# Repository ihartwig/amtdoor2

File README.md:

amtdoor2
========

This repository tracks files for AMT Door 2, an RFID based lock system in use at the [Ace Monster Toys](http://acemonstertoys.org/) hackspace in Oakland, CA. A complete description of the system these files are part of, [see the description on the AMT Wiki](http://wiki.acemonstertoys.org/Door#AMT_Door_2).

Included files:
* authCode - code to run on a raspberry pi or similar auth server
* housing - 2D drawings for assembly of the door tag reader
* hwTestCode - simplified panel mcu code to test clock settings
* panelMcuCode - firmware to run on the panel mcu that interprets RFID signals and accepts opening requests from the auth server
* physical - Eagle schematic/boards for the panel mcu

## Setting up on a 16u4:

to flash a new atmega16u4 for this code using an ISP (without the bootloader):

```
$ avrdude -p atmega16u4 -P usb -c avrispmkii -u -U lfuse:w:0xfc:m -U hfuse:w:0xd0:m -U efuse:w:0xc3:m
$ make MCU=atmega16u4
$ avrdude -p atmega16u4 -P usb -c avrispmkii -U flash:w:main.hex
```

to load the bootloader first using an ISP:

```
need to set fuses. we will copy from adafruit atmega32u4 dev board.
adafruit sets to: (E:C3, H:D0, L:FC) (avrdude-- has a typo)

Extended (0 is set):
7 1 Reserved
  1 Reserved
  0 Reserved
  0 Reserved
  0 HWBE          Hardware Boot Enable
  0 BODLEVEL2(1)  Brown-out Detector trigger level
  1 BODLEVEL1(1)  Brown-out Detector trigger level
0 1 BODLEVEL0(1)  Brown-out Detector trigger level

High (0 is set):
7 1 OCDEN         Enable OCD
  1 JTAGEN        Enable JTAG
  0 SPIEN         Enable Serial Program and Data Downloading
  1 WDTON         Watchdog Timer always on
  0 EESAVE        EEPROM memory is preserved through the Chip Erase
  0 BOOTSZ1       Select Boot Size (see Table 28-7 for details)
  0 BOOTSZ0       Select Boot Size (see Table 28-7 for details)
0 0 BOOTRST       Select Bootloader Address as Reset Vector

Low (0 is set):
7 1 CKDIV8        Divide clock by 8
  1 CKOUT         Clock output
  1 SUT1          Select start-up time
  1 SUT0          Select start-up time
  1 CKSEL3        Select Clock source
  1 CKSEL2        Select Clock source
  0 CKSEL1        Select Clock source
0 0 CKSEL0        Select Clock source
```

to compile CDC bootloader (from lufa-lib trunk):
for BOOTSZ1 = BOOTSZ0 = 0. see datasheet table 27-8.

```
$ make MCU=atmega16u4 BOOT_START=0x1800 F_CPU=16000000
$ mv BootloaderCDC.hex BootloaderCDC_16u4.hex
$ avrdude -p atmega16u4 -P usb -c avrispmkii -U flash:w:BootloaderCDC_16u4.hex
```

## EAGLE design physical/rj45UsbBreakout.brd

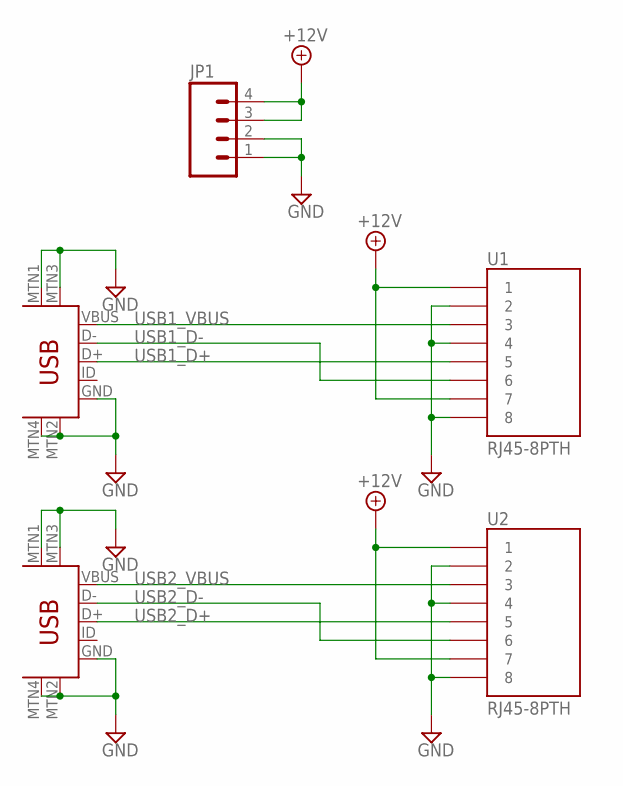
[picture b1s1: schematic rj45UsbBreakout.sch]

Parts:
JP1: M04LOCK; 1X04_LOCK
U1, U2: RJ45-8PTH; RJ45-8
U3, U4: USB-MINIB-5PIN; USB-MINIB

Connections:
+12V: JP1.3, JP1.4, U1.1, U1.7, U2.1, U2.7
GND: JP1.1, JP1.2, U1.2, U1.4, U1.8, U2.2, U2.4, U2.8, U3.GND, U3.MTN1 (MTN2), U3.MTN2 (MTN3), U3.MTN3 (MTN1), U3.MTN4, U4.GND, U4.MTN1 (MTN2), U4.MTN2 (MTN3), U4.MTN3 (MTN1), U4.MTN4
USB1_D+: U1.5, U3.D+
USB1_D-: U1.6, U3.D-
USB1_VBUS: U1.3, U3.VBUS
USB2_D+: U2.5, U4.D+
USB2_D-: U2.6, U4.D-
USB2_VBUS: U2.3, U4.VBUS

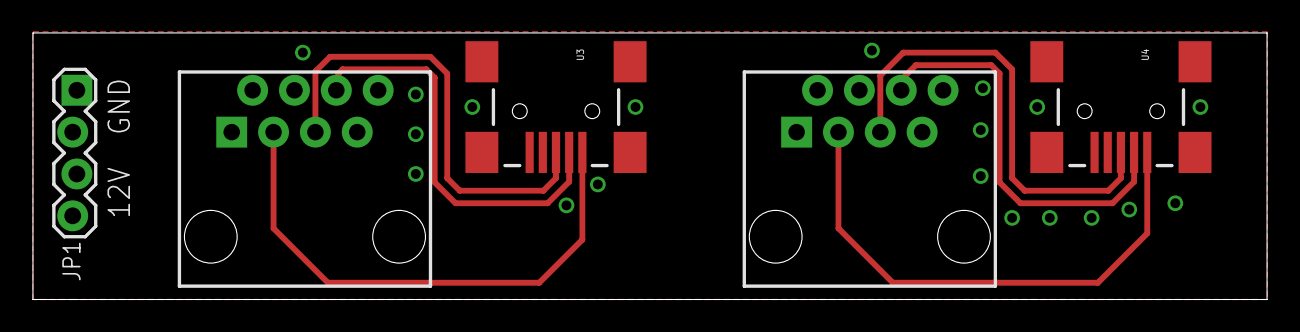
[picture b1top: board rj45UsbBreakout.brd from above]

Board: 2 copper layers, 74.9 x 16.2 mm, 5 parts (0 on the bottom side), 8 nets.

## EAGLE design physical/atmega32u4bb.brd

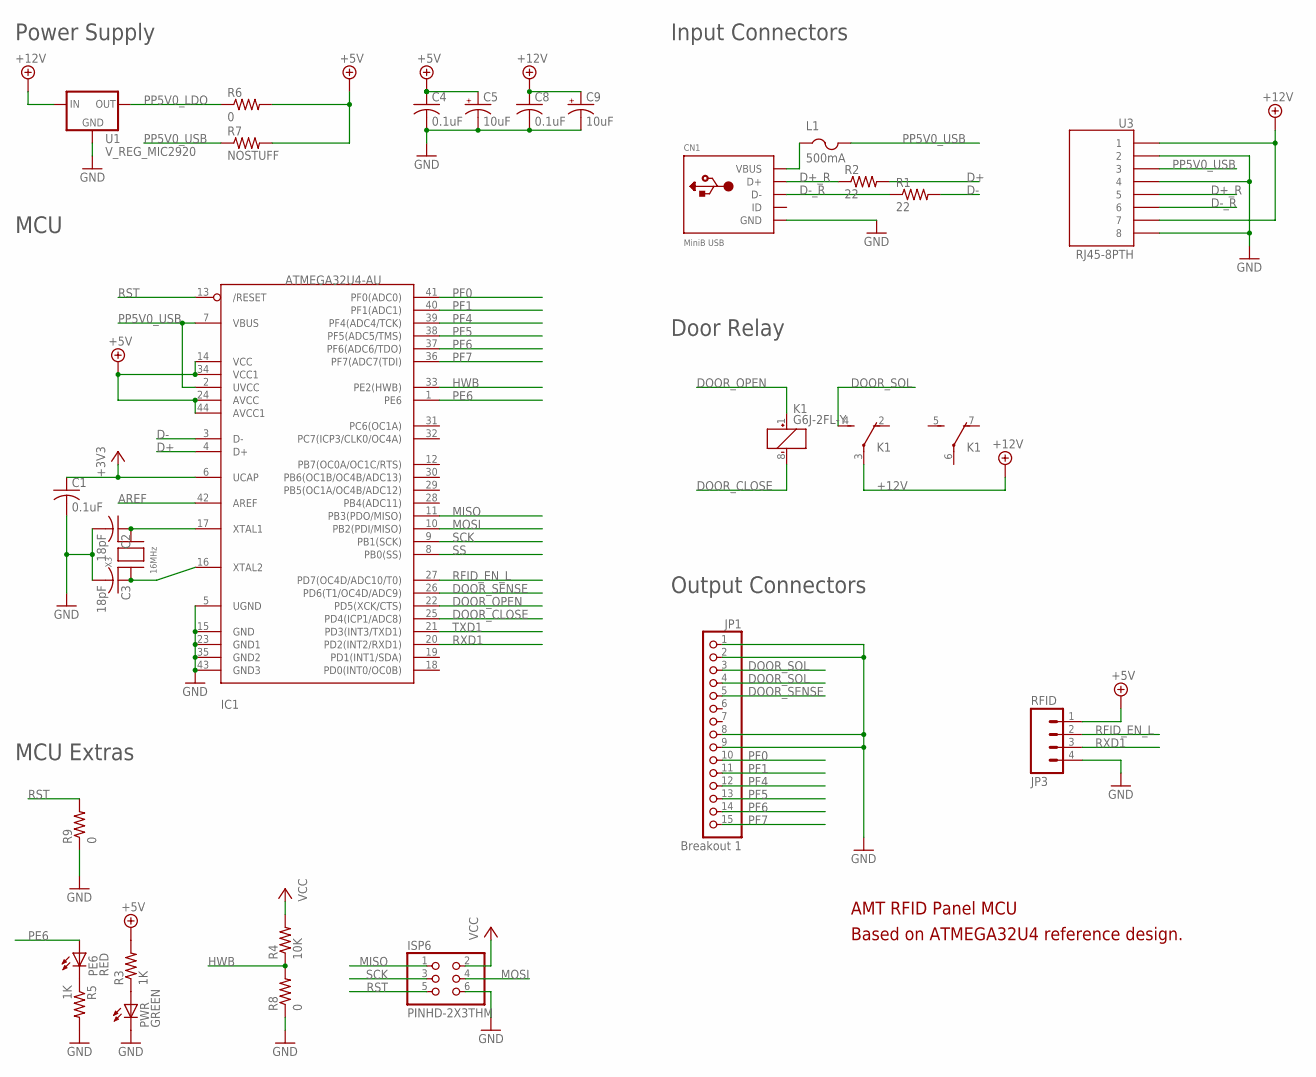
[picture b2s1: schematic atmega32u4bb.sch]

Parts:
C1, C4, C8: 0.1uF; C0805K
C2, C3: 18pF; C0805K
C5, C9: 10uF; A/3216-18R
CN1: MiniB USB; USB-MINIB
IC1: ATMEGA32U4-AU; TQFP44
ISP6: PINHD-2X3THM; ISP6
JP1: Breakout 1; 1X15-CB
JP3: RFID; 1X04_LOCK
K1: G6J-2FL-Y
L1: 500mA; R1206
PE6: RED; CHIPLED_0805
PWR: GREEN; CHIPLED_0805
R1, R2: 22; R0805
R3, R5: 1K; R0805
R4: 10K; R0805
R6, R8, R9: 0; R0805
R7: NOSTUFF; R0805
U1: V_REG_MIC2920; SOT223
U3: RJ45-8PTH; RJ45-8
X3: 16MHz; NX5032

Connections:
+3V3: C1.1, IC1.6 (UCAP)
+5V: C4.1, C5.+, IC1.14 (VCC), IC1.24 (AVCC), IC1.34 (VCC1), IC1.44 (AVCC1), JP3.1, R3.2, R6.2, R7.2
+12V: C8.1, C9.+, K1.3, U1.1 (IN), U3.1, U3.7
AREF: IC1.42 (AREF)
D+: IC1.4 (D+), R2.2
D+_R: CN1.D+, R2.1, U3.5
D-: IC1.3 (D-), R1.2
D-_R: CN1.D-, R1.1, U3.6
DOOR_CLOSE: IC1.25 (PD4(ICP1/ADC8)), K1.8 (-)
DOOR_OPEN: IC1.22 (PD5(XCK/CTS)), K1.1 (+)
DOOR_SENSE: IC1.26 (PD6(T1/OC4D/ADC9)), JP1.5
DOOR_SOL: JP1.3, JP1.4, K1.4 (S)
GND: C1.2, C2.2, C3.2, C4.2, C5.-, C8.2, C9.-, CN1.GND, IC1.5 (UGND), IC1.15 (GND), IC1.23 (GND1), IC1.35 (GND2), IC1.43 (GND3), ISP6.6, JP1.1, JP1.2, JP1.8, JP1.9, JP3.4, PWR.C, R5.2, R8.1, R9.1, U1.2 (GND), U1.4 (GND), U3.2, U3.4, U3.8
HWB: IC1.33 (PE2(HWB)), R4.1, R8.2
MISO: IC1.11 (PB3(PDO/MISO)), ISP6.1
MOSI: IC1.10 (PB2(PDI/MISO)), ISP6.4
unnamed: PWR.A, R3.1
unnamed: C2.1, IC1.17 (XTAL1), X3.P$2
unnamed: C3.1, IC1.16 (XTAL2), X3.P$1
unnamed: PE6.C, R5.1
PE6: IC1.1 (PE6), PE6.A
PF0: IC1.41 (PF0(ADC0)), JP1.10
PF1: IC1.40 (PF1(ADC1)), JP1.11
PF4: IC1.39 (PF4(ADC4/TCK)), JP1.12
PF5: IC1.38 (PF5(ADC5/TMS)), JP1.13
PF6: IC1.37 (PF6(ADC6/TDO)), JP1.14
PF7: IC1.36 (PF7(ADC7(TDI)), JP1.15
PP5V0_LDO: R6.1, U1.3 (OUT)
PP5V0_USB: IC1.2 (UVCC), IC1.7 (VBUS), L1.2, R7.1, U3.3
RFID_EN_L: IC1.27 (PD7(OC4D/ADC10/T0)), JP3.2
RST: IC1.13 (/RESET), ISP6.5, R9.2
RXD1: IC1.20 (PD2(INT2/RXD1)), JP3.3
SCK: IC1.9 (PB1(SCK)), ISP6.3
SS: IC1.8 (PB0(SS))
TXD1: IC1.21 (PD3(INT3/TXD1))
VBUS: CN1.VBUS, L1.1
VCC: ISP6.2, R4.2

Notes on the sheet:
AMT RFID Panel MCU
Based on ATMEGA32U4 reference design.
Power Supply
MCU
MCU Extras
Input Connectors
Door Relay
Output Connectors

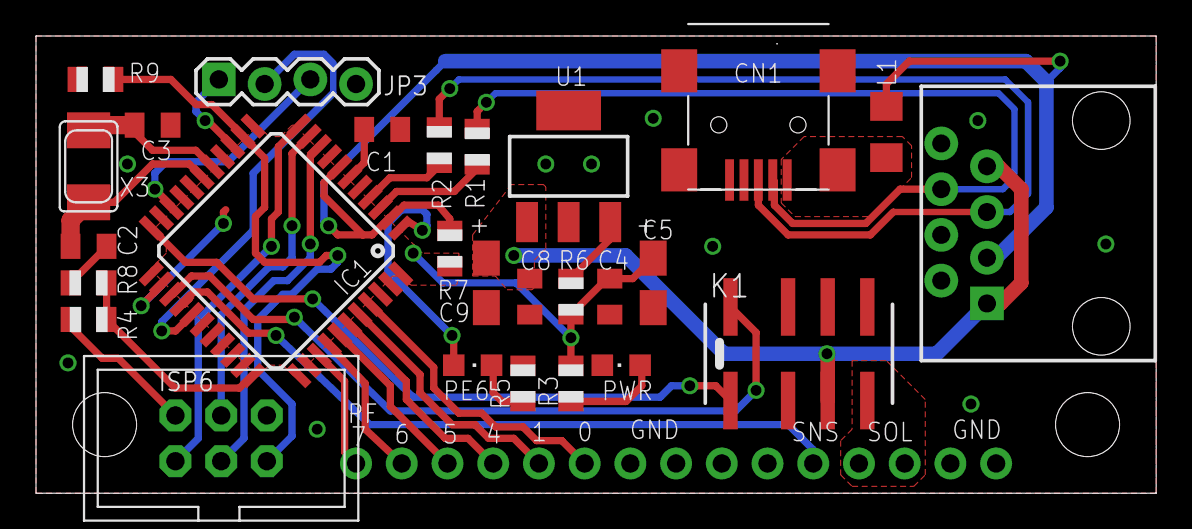
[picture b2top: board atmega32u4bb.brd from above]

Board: 2 copper layers, 62.2 x 25.4 mm, 28 parts (0 on the bottom side), 34 nets.

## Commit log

2014-05-31 attempt to ignore extra eagle files
2014-05-31 add rev 1 of controller and usb-rj45 breakout boards
2014-05-31 add external panel laser files
2014-06-01 update gitignore for micro programs
2014-06-01 add LUFA lib and skeleton code to start a virtual serial port
2014-06-04 implement virtual serial echo
2014-06-06 enough code to read the tag results back to computer
2014-06-06 code to parse and report tag
2014-06-08 implemented 1ms system timer
2014-06-08 support for authenticating and opening the door
2014-07-12 record debugging info on bootloading the 16u4
2014-07-13 add hw test and auth (raspberry pi/shevaplug) code
2014-07-13 add auto-run scripts
2014-07-13 update auth script paths. new setup script.
2014-07-13 chmod 755 door_test.sh in repo
2014-07-13 oops. fix missing $
2014-07-27 fix relay pin assignments. remove debug statements.
2014-07-27 tweak relay pulse length
2014-07-27 disable second led by default to conserve power/reduce thermal load on ldo
2014-07-27 rework the auth code files to auto-restart the door test check
2014-07-28 add auth code removal instructions
2014-07-28 push all doortestd output to log
2014-07-28 push all doortestd output to log (again)
2014-07-28 push all doortestd output to log (again again)
2014-07-28 push all doortestd output to log (again again again)
2014-08-07 add USB tests
2014-08-09 add new laser files for panel mcu (since this can't be outside)
2014-08-09 new auto-lock code
2014-10-20 update readme to point to new wiki page
2014-10-20 fix readme typo
2015-07-01 initial kicad project
2015-07-28 First major schematic/lib release. No board.
    - Add supporting docs for LTC4267/PoE circuit
    - Implement LTC4267-DC1145BF 12V PoE circuit
    - Add BeagleBone Black headers and docs
    - Add BBB cape required eeprom
    - Add necessary parts (H2019, LTC4267, LT1431, etc)
    - Updated netlist
2015-08-02 Fix PoE schematic, make major footprints, begin board grouping.
    * Swap RJ45 output for 2x3 .1" header. Use either small pcb or custom cable to connect to BBB.
    * Add footprints for ethernet jacks, transformers, large diodes/inductors, optoisolators, solder bridge.
    * Fix direction of optoisolator in feedback.
    * Fix power nFET symbol.
    * Fix incorrect ground on RJ45 shields.
    * Build symbol <-> footprint cmp file.
2016-09-11 fix panelMcuCode not reading the latest rfid tag
    The Parallax RFID reader sends tags of value XXXXXXXX in the format "\nXXXXXXXX\r". Since we handled \r\n by ignoring \r and reading \n we always left the most recent tag in the buffer. Now we read t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
2016-10-18 update panelmcu makefile for usbasp programmer

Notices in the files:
parts and their libraries:
SparkFun-Connectors: Licensing: CC v3.0 Share-Alike You are welcome to use this library for commercial purposes.
